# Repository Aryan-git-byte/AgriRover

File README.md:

# AgriRover
## it is a agriculture helping rover that can roam freely and autonoumously to map out the farmland's nutrient map.
Till now we have completed the Actuator Board, Radio Board and the carrier board of the PCB side. and Auger arm, Camera Head,Wheel, Wheel adaptor and LiDar on the CAD side.
this is our done project till now:
Werent able to push development in CAD this week much as abhinav was sick.
Here you can watch all the info of the PCB 

## Motor/Actuator Board:
It is the board responsible for the communication with all the actuators & motor in the rover, it features:
- An onboard programmable STM32G431R6Tx to control everything
- A CAN transceiver SN65HVD230 to add the ability of communicating to the STM32
- 5 (upto 3A) motor output, i m using them to control FIT0522 from DFrobot
- 6 headers [ 6V, SIGNAL, GND ] capable of 3A each servo headers, im using MG996R tho
### Schematic:

### PCB:

## Main Board:
It is the board with a CM4 onboard to perform all the CV things, calculations, handle LiDar, camera etc. it features:
- CM4 multi pin connector
- CAN transceiver, MCP2515-xST with SN65HVD230
- a 22 pin camera header
- a fan controller
- a USB, HDMI, and Ethernet for debugging.
- LiDar Header
- SD card
- Onboard IMU ISM330DHCX
### Schematic:

### PCB:

## Radio Board
it is the board responsible for communication with the transmitter and the HTTPS through LTE, it features:
- A 40 pin rpi connector, so you can plug it in any rpi
- a SIM7080G with GNSS and RF antenna sma connectors
- a E22-900M22S with SMA connector and UFL both, so whatever u choose
### Schematic:

### PCB:

## Camera Head:

## Auger arm:

## Wheels:

# Journals:
you can read the journals of respective collaborators in the root of this repo as [NAME]-JOURNAL.md
# Roadmap:
- [x] Complete the CM4 Carrier Board by Next week
- [ ] Complete the Chasis till Next week
- [x] fix all the DRC error by this time in the main carrier board
- [ ] make the Power Board 💀 (30A+)
- [x] make the communication board
- [ ] assemble all the individual components in the CAD
[ Abhinav left as he was sick for this week, altho would work on the project tho in future ig ]

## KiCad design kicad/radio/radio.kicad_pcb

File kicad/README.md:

# KiCad Designs

This directory contains all KiCad circuit designs and schematics for the AgriRover project.

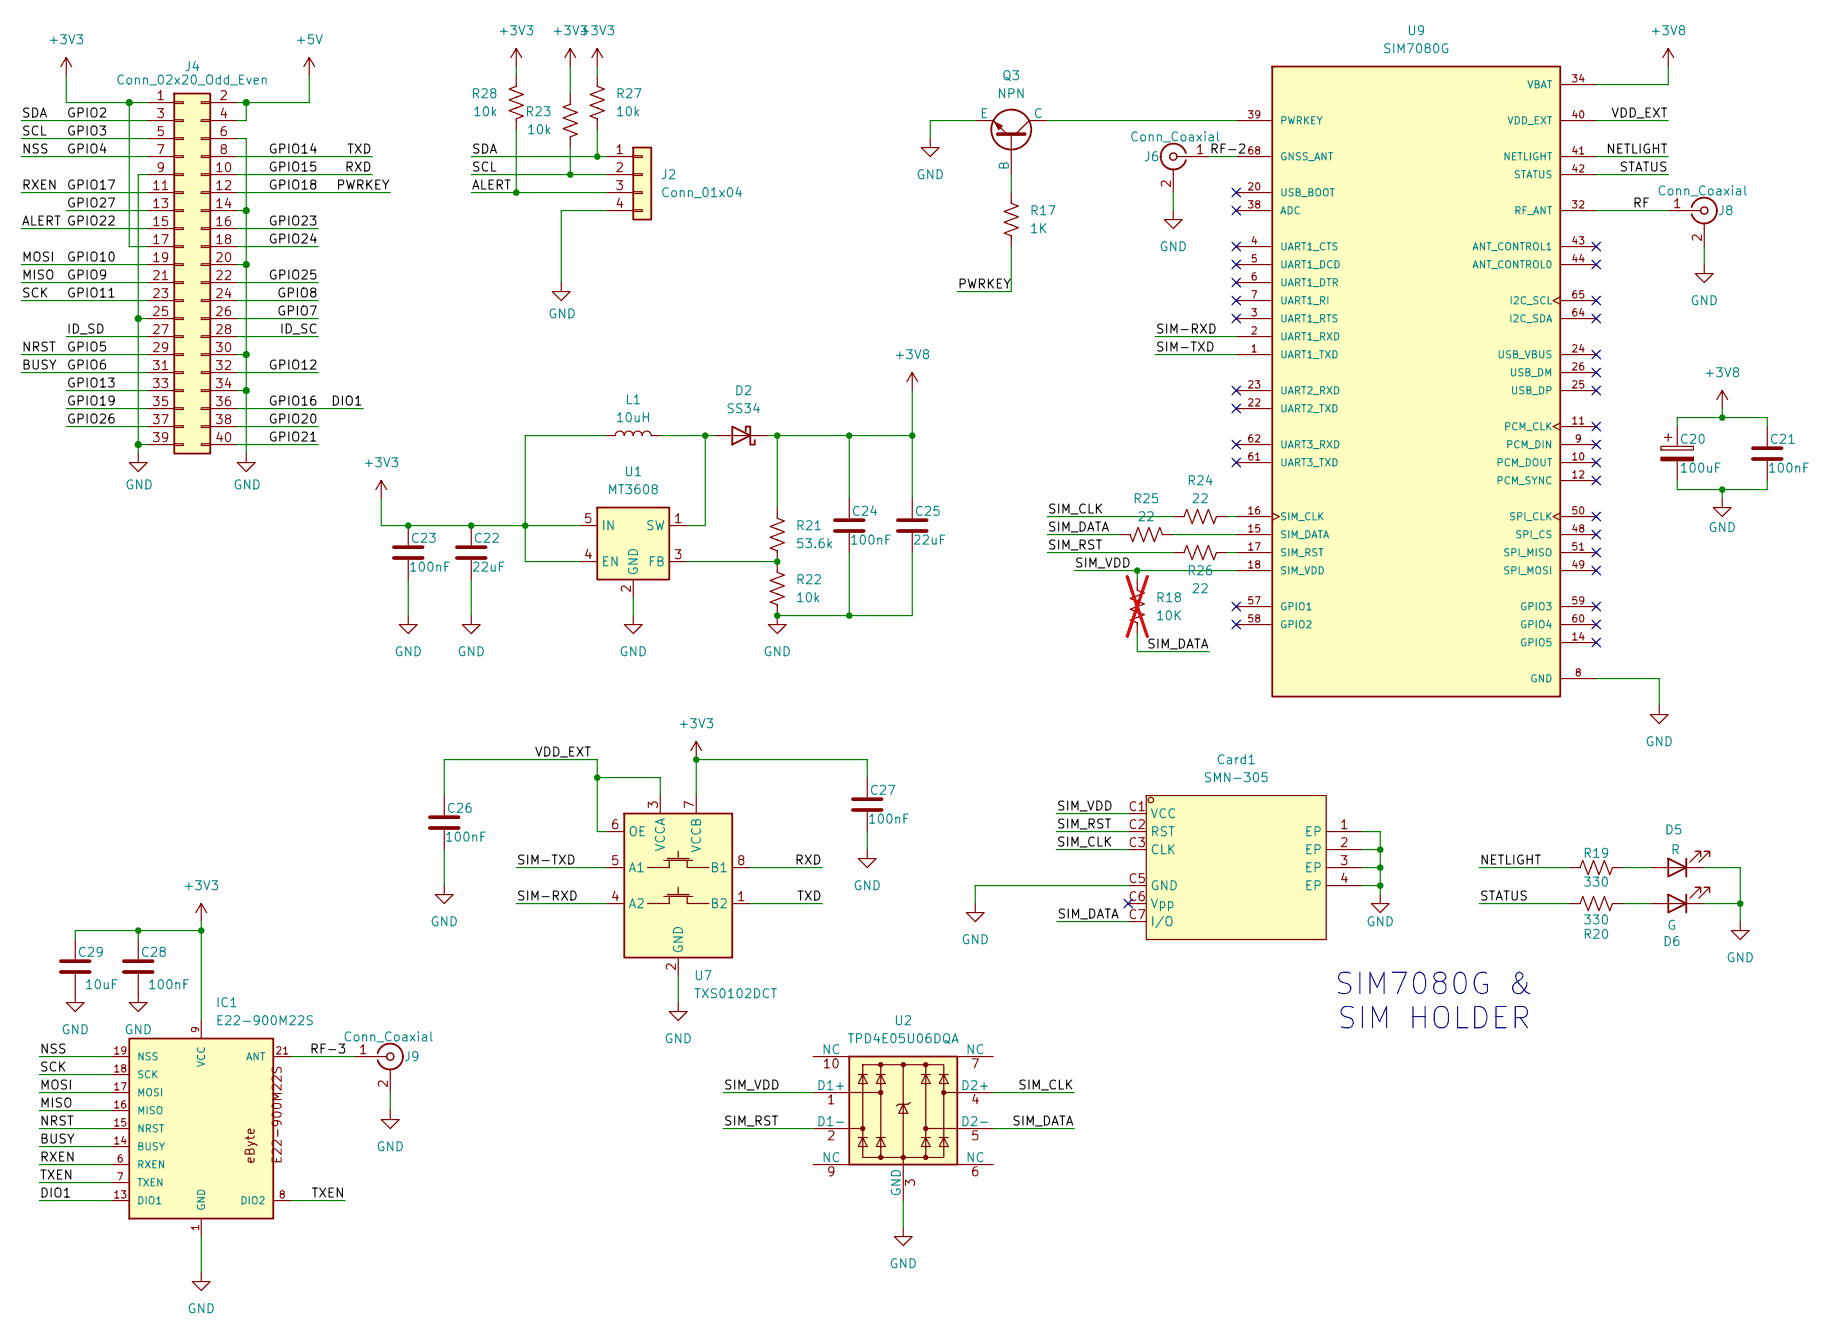
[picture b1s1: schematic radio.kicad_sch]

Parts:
C20: 100uF; CP_EIA-3528-21_Kemet-B_HandSolder
C21, C23, C24, C26, C27, C28: 100nF; C_0805_2012Metric_Pad1.18x1.45mm_HandSolder
C22, C25: 22uF; C_0805_2012Metric_Pad1.18x1.45mm_HandSolder
C29: 10uF; C_0805_2012Metric_Pad1.18x1.45mm_HandSolder
Card1: SMN-305; SIM-SMD_SMN-305; MPN SMN-305; LCSC Part C266890
D2: SS34; D_SMA
D5: R; LED_0805_2012Metric_Pad1.15x1.40mm_HandSolder
D6: G; LED_0805_2012Metric_Pad1.15x1.40mm_HandSolder
IC1: E22-900M22S
J2: Conn_01x04; JST_XH_B4B-XH-A_1x04_P2.50mm_Vertical
J4: Conn_02x20_Odd_Even; PinSocket_2x20_P2.54mm_Vertical; Part Description PinHeader_2x20_P2.54mm_Vertical
J6, J8, J9: Conn_Coaxial; SMA_Amphenol_132289_EdgeMount
L1: 10uH; L_7.3x7.3_H4.5
Q3: NPN; SOT-23
R17: 1K; R_0805_2012Metric_Pad1.20x1.40mm_HandSolder
R18: 10K; R_0805_2012Metric_Pad1.20x1.40mm_HandSolder; not fitted
R19, R20: 330; R_0805_2012Metric_Pad1.20x1.40mm_HandSolder
R21: 53.6k; R_0805_2012Metric_Pad1.20x1.40mm_HandSolder
R22, R23, R27, R28: 10k; R_0805_2012Metric_Pad1.20x1.40mm_HandSolder
R24, R25, R26: 22; R_0805_2012Metric_Pad1.20x1.40mm_HandSolder
U1: MT3608; SOT-23-6
U2: TPD4E05U06DQA; USON-10_2.5x1.0mm_P0.5mm
U7: TXS0102DCT; SSOP-8_2.95x2.8mm_P0.65mm
U9: SIM7080G; XCVR_SIM7080G

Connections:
+3V3: C22.1, C23.1, C27.1, C28.1, C29.1, IC1.9 (VCC), J4.1, J4.17, L1.1, R23.1, R27.1, R28.1, U1.4 (EN), U1.5 (IN), U7.7 (VCCB)
+3V8: C20.1, C21.1, C24.1, C25.1, D2.1 (K), R21.1, U9.34 (VBAT), U9.35 (VBAT)
+5V: J4.2, J4.4
/ALERT: J2.3, J4.15, R28.2
/BUSY: IC1.14 (BUSY), J4.31
/DIO1: IC1.13 (DIO1), J4.36
/GPIO2: J2.1, J4.3, R27.2
/GPIO3: J2.2, J4.5, R23.2
/GPIO4: IC1.19 (NSS), J4.7
/GPIO5: IC1.15 (NRST), J4.29
/GPIO7: J4.26
/GPIO8: J4.24
/GPIO9: IC1.16 (MISO), J4.21
/GPIO10: IC1.17 (MOSI), J4.19
/GPIO11: IC1.18 (SCK), J4.23
/GPIO12: J4.32
/GPIO13: J4.33
/GPIO14: J4.8, U7.1 (B2)
/GPIO15: J4.10, U7.8 (B1)
/GPIO17: IC1.6 (RXEN), J4.11
/GPIO18: J4.12, R17.2
/GPIO19: J4.35
/GPIO20: J4.38
/GPIO21: J4.40
/GPIO23: J4.16
/GPIO24: J4.18
/GPIO25: J4.22
/GPIO26: J4.37
/GPIO27: J4.13
/ID_SC: J4.28
/ID_SD: J4.27
/NETLIGHT: R19.1, U9.41 (NETLIGHT)
/RF: J8.1 (In), U9.32 (RF_ANT)
/RF-2: J6.1 (In), U9.68 (GNSS_ANT)
/RF-3: IC1.21 (ANT), J9.1 (In)
/SIM-RXD: U7.4 (A2), U9.2 (UART1_RXD)
/SIM-TXD: U7.5 (A1), U9.1 (UART1_TXD)
/SIM_CLK: Card1.C3 (CLK), R24.1, U2.4 (D2+)
/SIM_DATA: Card1.C7 (I/O), R18.2, R25.1, U2.5 (D2-)
/SIM_RST: Card1.C2 (RST), R26.1, U2.2 (D1-)
/SIM_VDD: Card1.C1 (VCC), R18.1, U2.1 (D1+), U9.18 (SIM_VDD)
/STATUS: R20.1, U9.42 (STATUS)
/TXEN: IC1.7 (TXEN), IC1.8 (DIO2)
/VDD_EXT: C26.1, U7.3 (VCCA), U7.6 (OE), U9.40 (VDD_EXT)
GND: C20.2, C21.2, C22.2, C23.2, C24.2, C25.2, C26.2, C27.2, C28.2, C29.2, Card1.1 (EP), Card1.2 (EP), Card1.3 (EP), Card1.4 (EP), Card1.C5 (GND), D5.1 (K), D6.1 (K), IC1.1 (GND), IC1.2 (GND), IC1.3 (GND), IC1.4 (GND), IC1.5 (GND), IC1.10 (GND), IC1.11 (GND), IC1.12 (GND), IC1.20 (GND), IC1.22 (GND), J2.4, J4.6, J4.9, J4.14, J4.20, J4.25, J4.30, J4.34, J4.39, J6.2 (Ext), J8.2 (Ext), J9.2 (Ext), Q3.3 (E), R22.2, U1.2 (GND), U2.3 (GND), U2.8 (GND), U7.2 (GND), U9.8 (GND), U9.13 (GND), U9.19 (GND), U9.21 (GND), U9.27 (GND), U9.28 (NC), U9.29 (NC), U9.30 (GND), U9.31 (GND), U9.33 (GND), U9.36 (GND), U9.37 (GND), U9.45 (GND), U9.46 (NC), U9.47 (NC), U9.52 (NC), U9.53 (NC), U9.54 (NC), U9.55 (NC), U9.56 (NC), U9.63 (GND), U9.66 (GND), U9.67 (GND), U9.69 (GND), U9.70 (GND), U9.71 (GND), U9.72 (GND), U9.73 (GND), U9.74 (GND), U9.75 (GND), U9.76 (GND), U9.77 (GND)
unnamed: D2.2 (A), L1.2, U1.1 (SW)
unnamed: D5.2 (A), R19.2
unnamed: D6.2 (A), R20.2
unnamed: Q3.2 (B), R17.1
unnamed: Q3.1 (C), U9.39 (PWRKEY)
unnamed: R21.2, R22.1, U1.3 (FB)
unnamed: R24.2, U9.16 (SIM_CLK)
unnamed: R25.2, U9.15 (SIM_DATA)
unnamed: R26.2, U9.17 (SIM_RST)

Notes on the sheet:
SIM7080G & SIM HOLDER

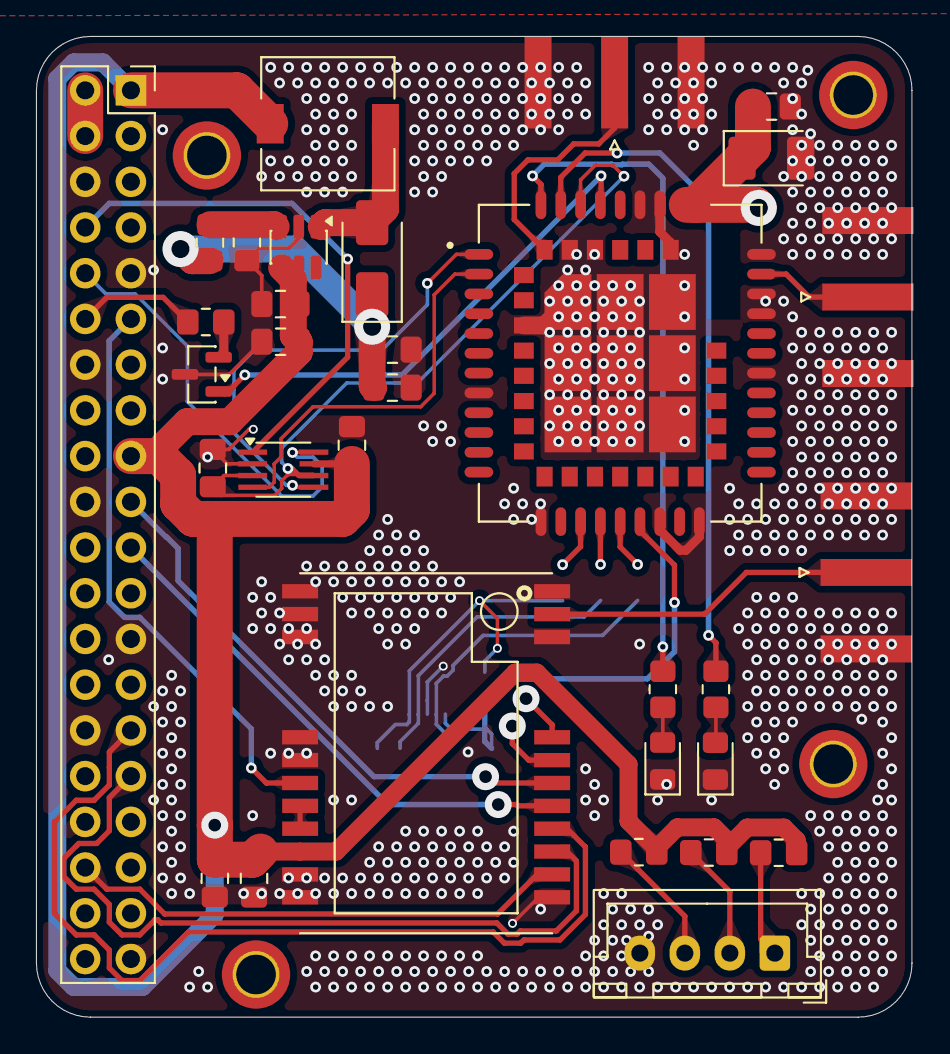
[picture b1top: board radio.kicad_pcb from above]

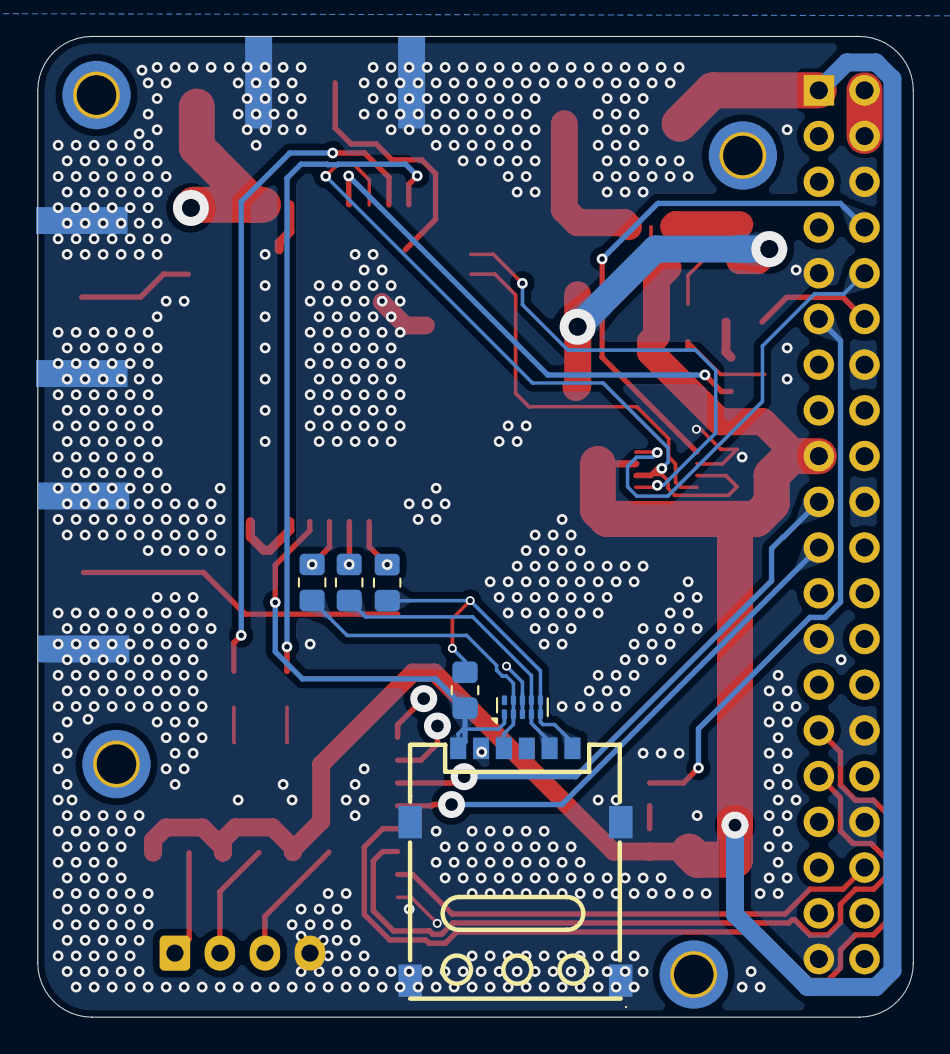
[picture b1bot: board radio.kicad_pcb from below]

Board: 4 copper layers, 48.6 x 54.5 mm, 38 parts (6 on the bottom side), 40 nets.

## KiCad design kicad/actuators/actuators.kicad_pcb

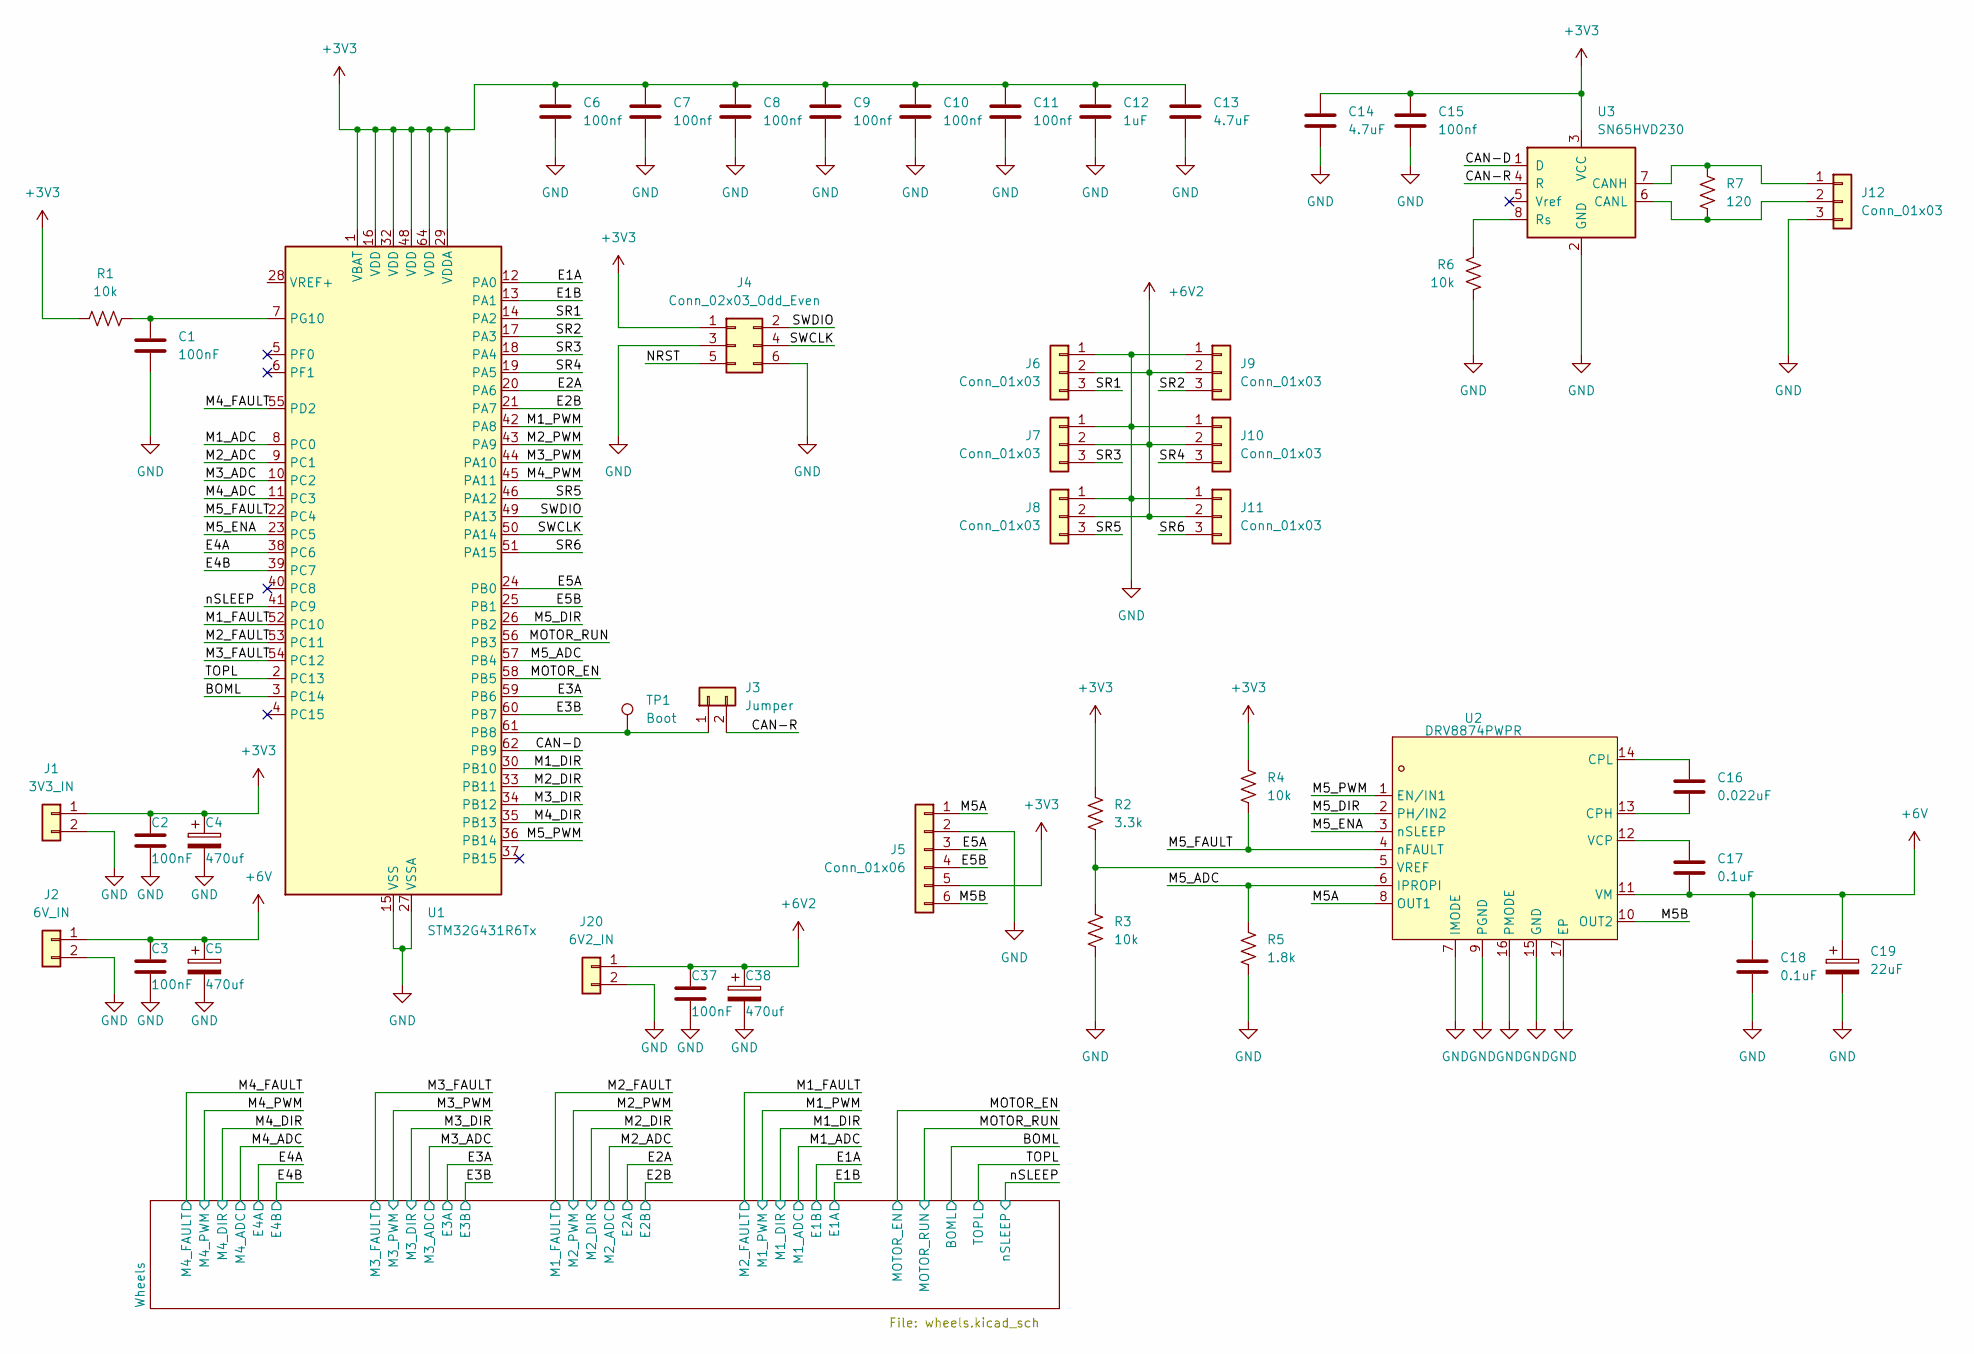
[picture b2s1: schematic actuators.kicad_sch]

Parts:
C1, C2, C3, C37: 100nF; C_0603_1608Metric
C4, C5, C38: 470uf; CP_Elec_10x10.5
C6, C7, C8, C9, C10, C11, C15: 100nf; C_0603_1608Metric
C12: 1uF; C_0603_1608Metric
C13, C14: 4.7uF; C_0603_1608Metric
C16: 0.022uF; C_0603_1608Metric
C17, C18: 0.1uF; C_0603_1608Metric
C19: 22uF; CP_Elec_5x5.3
J1: 3V3_IN; AMASS_XT30U-M_1x02_P5.0mm_Vertical
J2: 6V_IN; AMASS_XT30U-M_1x02_P5.0mm_Vertical
J3: Jumper; PinHeader_1x02_P2.54mm_Vertical
J4: Conn_02x03_Odd_Even; PinHeader_2x03_P2.54mm_Vertical
J5: Conn_01x06; PinHeader_1x06_P2.54mm_Vertical
J6, J7, J8, J9, J10, J11, J12: Conn_01x03; PinSocket_1x03_P2.54mm_Vertical
J20: 6V2_IN; AMASS_XT30U-M_1x02_P5.0mm_Vertical
R1, R3, R4, R6: 10k; R_0603_1608Metric
R2: 3.3k; R_0603_1608Metric
R5: 1.8k; R_0603_1608Metric
R7: 120; R_0603_1608Metric
TP1: Boot; TestPoint_Pad_1.5x1.5mm
U1: STM32G431R6Tx; LQFP-64_10x10mm_P0.5mm
U2: DRV8874PWPR; HTSSOP-16_L5.0-W4.4-P0.65-LS6.4-BL-EP; MPN DRV8874PWPR; LCSC Part C1855818
U3: SN65HVD230; SOIC-8_3.9x4.9mm_P1.27mm

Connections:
+3V3: C2.1, C4.1, C6.1, C7.1, C8.1, C9.1, C10.1, C11.1, C12.1, C13.1, C14.1, C15.1, J1.1, J4.1, J5.5, R1.1, R2.1, R4.1, U1.1 (VBAT), U1.16 (VDD), U1.29 (VDDA), U1.32 (VDD), U1.48 (VDD), U1.64 (VDD), U3.3 (VCC); also elsewhere on the board
+6V: C3.1, C5.1, C17.2, C18.1, C19.1, J2.1, U2.11 (VM); also elsewhere on the board
+6V2: C37.1, C38.1, J6.2, J7.2, J8.2, J9.2, J10.2, J11.2, J20.1
/BOML: U1.3 (PC14); also elsewhere on the board
/CAN-D: U1.62 (PB9), U3.1 (D)
/CAN-R: J3.2, U3.4 (R)
/E1A: U1.12 (PA0); also elsewhere on the board
/E1B: U1.13 (PA1); also elsewhere on the board
/E2A: U1.20 (PA6); also elsewhere on the board
/E2B: U1.21 (PA7); also elsewhere on the board
/E3A: U1.59 (PB6); also elsewhere on the board
/E3B: U1.60 (PB7); also elsewhere on the board
/E4A: U1.38 (PC6); also elsewhere on the board
/E4B: U1.39 (PC7); also elsewhere on the board
/E5A: J5.3, U1.24 (PB0)
/E5B: J5.4, U1.25 (PB1)
/M1_ADC: U1.8 (PC0); also elsewhere on the board
/M1_DIR: U1.30 (PB10); also elsewhere on the board
/M1_FAULT: U1.52 (PC10); also elsewhere on the board
/M1_PWM: U1.42 (PA8); also elsewhere on the board
/M2_ADC: U1.9 (PC1); also elsewhere on the board
/M2_DIR: U1.33 (PB11); also elsewhere on the board
/M2_FAULT: U1.53 (PC11); also elsewhere on the board
/M2_PWM: U1.43 (PA9); also elsewhere on the board
/M3_ADC: U1.10 (PC2); also elsewhere on the board
/M3_DIR: U1.34 (PB12); also elsewhere on the board
/M3_FAULT: U1.54 (PC12); also elsewhere on the board
/M3_PWM: U1.44 (PA10); also elsewhere on the board
/M4_ADC: U1.11 (PC3); also elsewhere on the board
/M4_DIR: U1.35 (PB13); also elsewhere on the board
/M4_FAULT: U1.55 (PD2); also elsewhere on the board
/M4_PWM: U1.45 (PA11); also elsewhere on the board
/M5A: J5.1, U2.8 (OUT1)
/M5B: J5.6, U2.10 (OUT2)
/M5_ADC: R5.1, U1.57 (PB4), U2.6 (IPROPI)
/M5_DIR: U1.26 (PB2), U2.2 (PH/IN2)
/M5_ENA: U1.23 (PC5), U2.3 (nSLEEP)
/M5_FAULT: R4.2, U1.22 (PC4), U2.4 (nFAULT)
/M5_PWM: U1.36 (PB14), U2.1 (EN/IN1)
/MOTOR_EN: U1.58 (PB5); also elsewhere on the board
/MOTOR_RUN: U1.56 (PB3); also elsewhere on the board
/NRST: J4.5
/SR1: J6.3, U1.14 (PA2)
/SR2: J9.3, U1.17 (PA3)
/SR3: J7.3, U1.18 (PA4)
/SR4: J10.3, U1.19 (PA5)
/SR5: J8.3, U1.46 (PA12)
/SR6: J11.3, U1.51 (PA15)
/SWCLK: J4.4, U1.50 (PA14)
/SWDIO: J4.2, U1.49 (PA13)
/TOPL: U1.2 (PC13); also elsewhere on the board
/nSLEEP: U1.41 (PC9); also elsewhere on the board
GND: C1.2, C2.2, C3.2, C4.2, C5.2, C6.2, C7.2, C8.2, C9.2, C10.2, C11.2, C12.2, C13.2, C14.2, C15.2, C18.2, C19.2, C37.2, C38.2, J1.2, J2.2, J4.3, J4.6, J5.2, J6.1, J7.1, J8.1, J9.1, J10.1, J11.1, J12.3, J20.2, R3.2, R5.2, R6.1, U1.15 (VSS), U1.27 (VSSA), U1.31 (VSS), U1.47 (VSS), U1.63 (VSS), U2.7 (IMODE), U2.9 (PGND), U2.15 (GND), U2.16 (PMODE), U2.17 (EP), U3.2 (GND); also elsewhere on the board
unnamed: J3.1, TP1.1 (1_1), U1.61 (PB8)
unnamed: J12.1, R7.2, U3.7 (CANH)
unnamed: J12.2, R7.1, U3.6 (CANL)
unnamed: C1.1, R1.2, U1.7 (PG10)
unnamed: C16.2, U2.13 (CPH)
unnamed: C16.1, U2.14 (CPL)
unnamed: C17.1, U2.12 (VCP)
unnamed: R2.2, R3.1, U2.5 (VREF)
unnamed: R6.2, U3.8 (Rs)

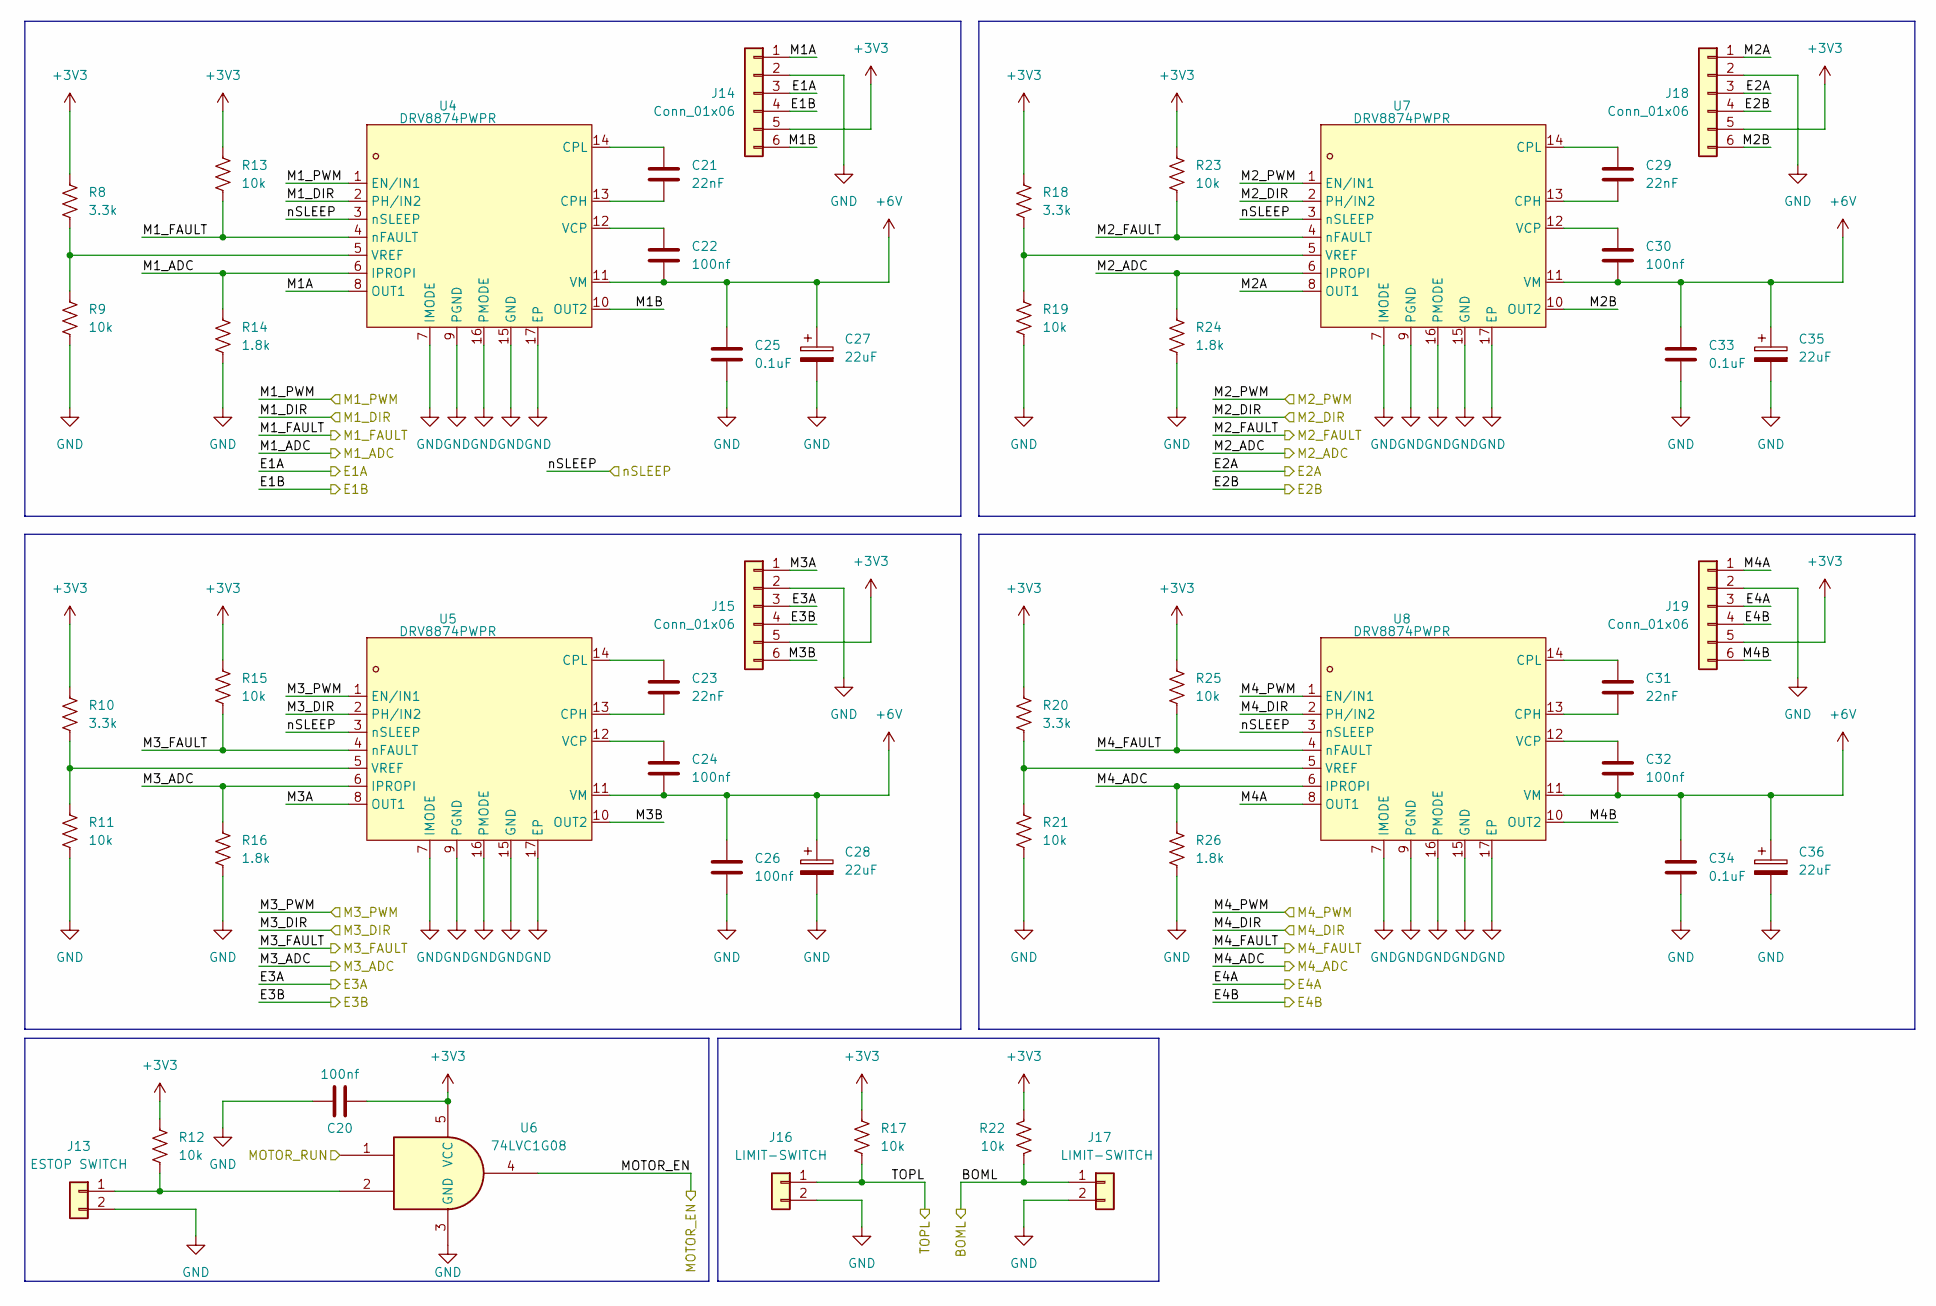
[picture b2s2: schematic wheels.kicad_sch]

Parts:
C20, C22, C24, C26, C30, C32: 100nf; C_0603_1608Metric
C21, C23, C29, C31: 22nF; C_0603_1608Metric
C25, C33, C34: 0.1uF; C_0603_1608Metric
C27, C28, C35, C36: 22uF; CP_Elec_5x5.3
J13: ESTOP SWITCH; PinHeader_1x02_P2.54mm_Vertical
J14, J15, J18, J19: Conn_01x06; PinHeader_1x06_P2.54mm_Vertical
J16, J17: LIMIT-SWITCH; PinHeader_1x02_P2.54mm_Vertical
R8, R10, R18, R20: 3.3k; R_0603_1608Metric
R9, R11, R12, R13, R15, R17, R19, R21, R22, R23, R25: 10k; R_0603_1608Metric
R14, R16, R24, R26: 1.8k; R_0603_1608Metric
U4, U5, U7, U8: DRV8874PWPR; HTSSOP-16_L5.0-W4.4-P0.65-LS6.4-BL-EP; MPN DRV8874PWPR; LCSC Part C1855818
U6: 74LVC1G08; SOT-23-5

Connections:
+3V3: C20.2, J14.5, J15.5, J18.5, J19.5, R8.1, R10.1, R12.2, R13.1, R15.1, R17.2, R18.1, R20.1, R22.2, R23.1, R25.1, U6.5 (VCC); also elsewhere on the board
+6V: C22.2, C24.2, C25.1, C26.1, C27.1, C28.1, C30.2, C32.2, C33.1, C34.1, C35.1, C36.1, U4.11 (VM), U5.11 (VM), U7.11 (VM), U8.11 (VM); also elsewhere on the board
/BOML: J17.1, R22.1; also elsewhere on the board
/E1A: J14.4; also elsewhere on the board
/E1B: J14.3; also elsewhere on the board
/E2A: J18.3; also elsewhere on the board
/E2B: J18.4; also elsewhere on the board
/E3A: J15.3; also elsewhere on the board
/E3B: J15.4; also elsewhere on the board
/E4A: J19.3; also elsewhere on the board
/E4B: J19.4; also elsewhere on the board
/M1_ADC: R14.1, U4.6 (IPROPI); also elsewhere on the board
/M1_DIR: U4.2 (PH/IN2); also elsewhere on the board
/M1_FAULT: R23.2, U7.4 (nFAULT); also elsewhere on the board
/M1_PWM: U4.1 (EN/IN1); also elsewhere on the board
/M2_ADC: R24.1, U7.6 (IPROPI); also elsewhere on the board
/M2_DIR: U7.2 (PH/IN2); also elsewhere on the board
/M2_FAULT: R13.2, U4.4 (nFAULT); also elsewhere on the board
/M2_PWM: U7.1 (EN/IN1); also elsewhere on the board
/M3_ADC: R16.1, U5.6 (IPROPI); also elsewhere on the board
/M3_DIR: U5.2 (PH/IN2); also elsewhere on the board
/M3_FAULT: R15.2, U5.4 (nFAULT); also elsewhere on the board
/M3_PWM: U5.1 (EN/IN1); also elsewhere on the board
/M4_ADC: R26.1, U8.6 (IPROPI); also elsewhere on the board
/M4_DIR: U8.2 (PH/IN2); also elsewhere on the board
/M4_FAULT: R25.2, U8.4 (nFAULT); also elsewhere on the board
/M4_PWM: U8.1 (EN/IN1); also elsewhere on the board
/MOTOR_EN: U6.4; also elsewhere on the board
/MOTOR_RUN: U6.1; also elsewhere on the board
/TOPL: J16.1, R17.1; also elsewhere on the board
/Wheels/M1A: J14.1, U4.8 (OUT1)
/Wheels/M1B: J14.6, U4.10 (OUT2)
/Wheels/M2A: J18.1, U7.8 (OUT1)
/Wheels/M2B: J18.6, U7.10 (OUT2)
/Wheels/M3A: J15.1, U5.8 (OUT1)
/Wheels/M3B: J15.6, U5.10 (OUT2)
/Wheels/M4A: J19.1, U8.8 (OUT1)
/Wheels/M4B: J19.6, U8.10 (OUT2)
/nSLEEP: U4.3 (nSLEEP), U5.3 (nSLEEP), U7.3 (nSLEEP), U8.3 (nSLEEP); also elsewhere on the board
GND: C20.1, C25.2, C26.2, C27.2, C28.2, C33.2, C34.2, C35.2, C36.2, J13.2, J14.2, J15.2, J16.2, J17.2, J18.2, J19.2, R9.2, R11.2, R14.2, R16.2, R19.2, R21.2, R24.2, R26.2, U4.7 (IMODE), U4.9 (PGND), U4.15 (GND), U4.16 (PMODE), U4.17 (EP), U5.7 (IMODE), U5.9 (PGND), U5.15 (GND), U5.16 (PMODE), U5.17 (EP), U6.3 (GND), U7.7 (IMODE), U7.9 (PGND), U7.15 (GND), U7.16 (PMODE), U7.17 (EP), U8.7 (IMODE), U8.9 (PGND), U8.15 (GND), U8.16 (PMODE), U8.17 (EP); also elsewhere on the board
unnamed: J13.1, R12.1, U6.2
unnamed: C21.2, U4.13 (CPH)
unnamed: C21.1, U4.14 (CPL)
unnamed: C22.1, U4.12 (VCP)
unnamed: R8.2, R9.1, U4.5 (VREF)
unnamed: C23.2, U5.13 (CPH)
unnamed: C23.1, U5.14 (CPL)
unnamed: C24.1, U5.12 (VCP)
unnamed: R10.2, R11.1, U5.5 (VREF)
unnamed: C29.2, U7.13 (CPH)
unnamed: C29.1, U7.14 (CPL)
unnamed: C30.1, U7.12 (VCP)
unnamed: R18.2, R19.1, U7.5 (VREF)
unnamed: C31.2, U8.13 (CPH)
unnamed: C31.1, U8.14 (CPL)
unnamed: C32.1, U8.12 (VCP)
unnamed: R20.2, R21.1, U8.5 (VREF)

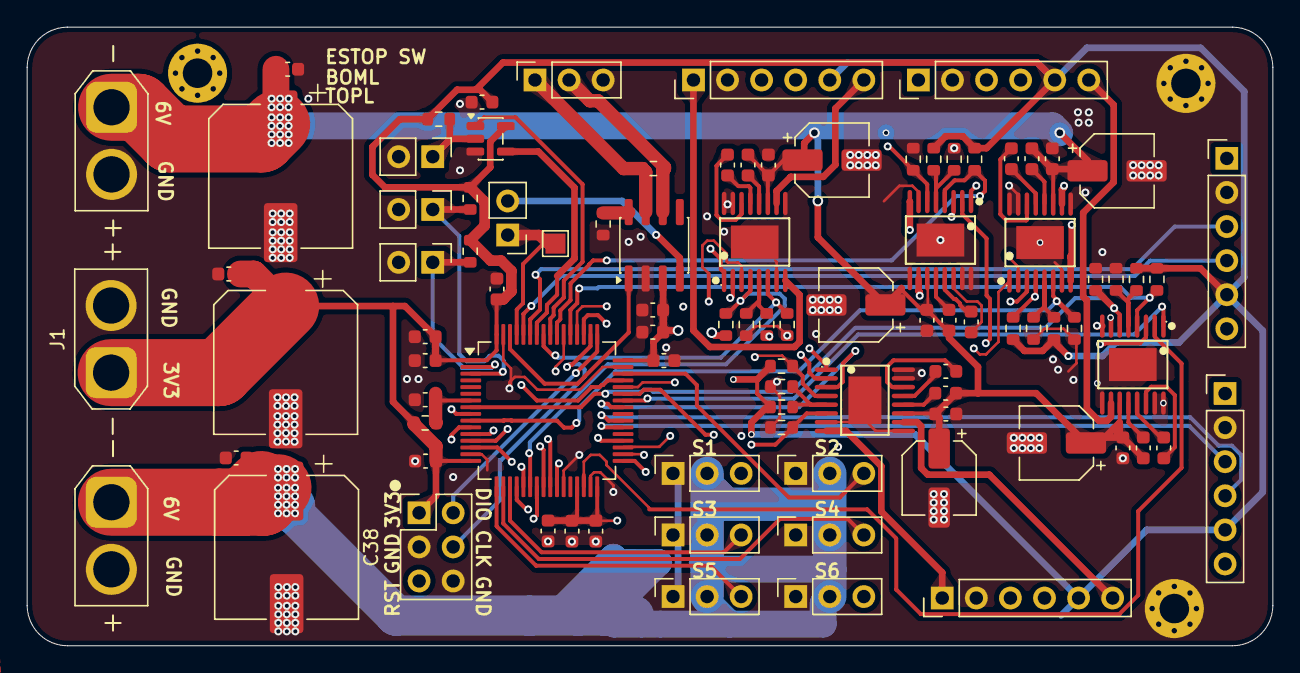
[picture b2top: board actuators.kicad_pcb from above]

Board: 4 copper layers, 92.8 x 46.1 mm, 93 parts (0 on the bottom side), 86 nets.
